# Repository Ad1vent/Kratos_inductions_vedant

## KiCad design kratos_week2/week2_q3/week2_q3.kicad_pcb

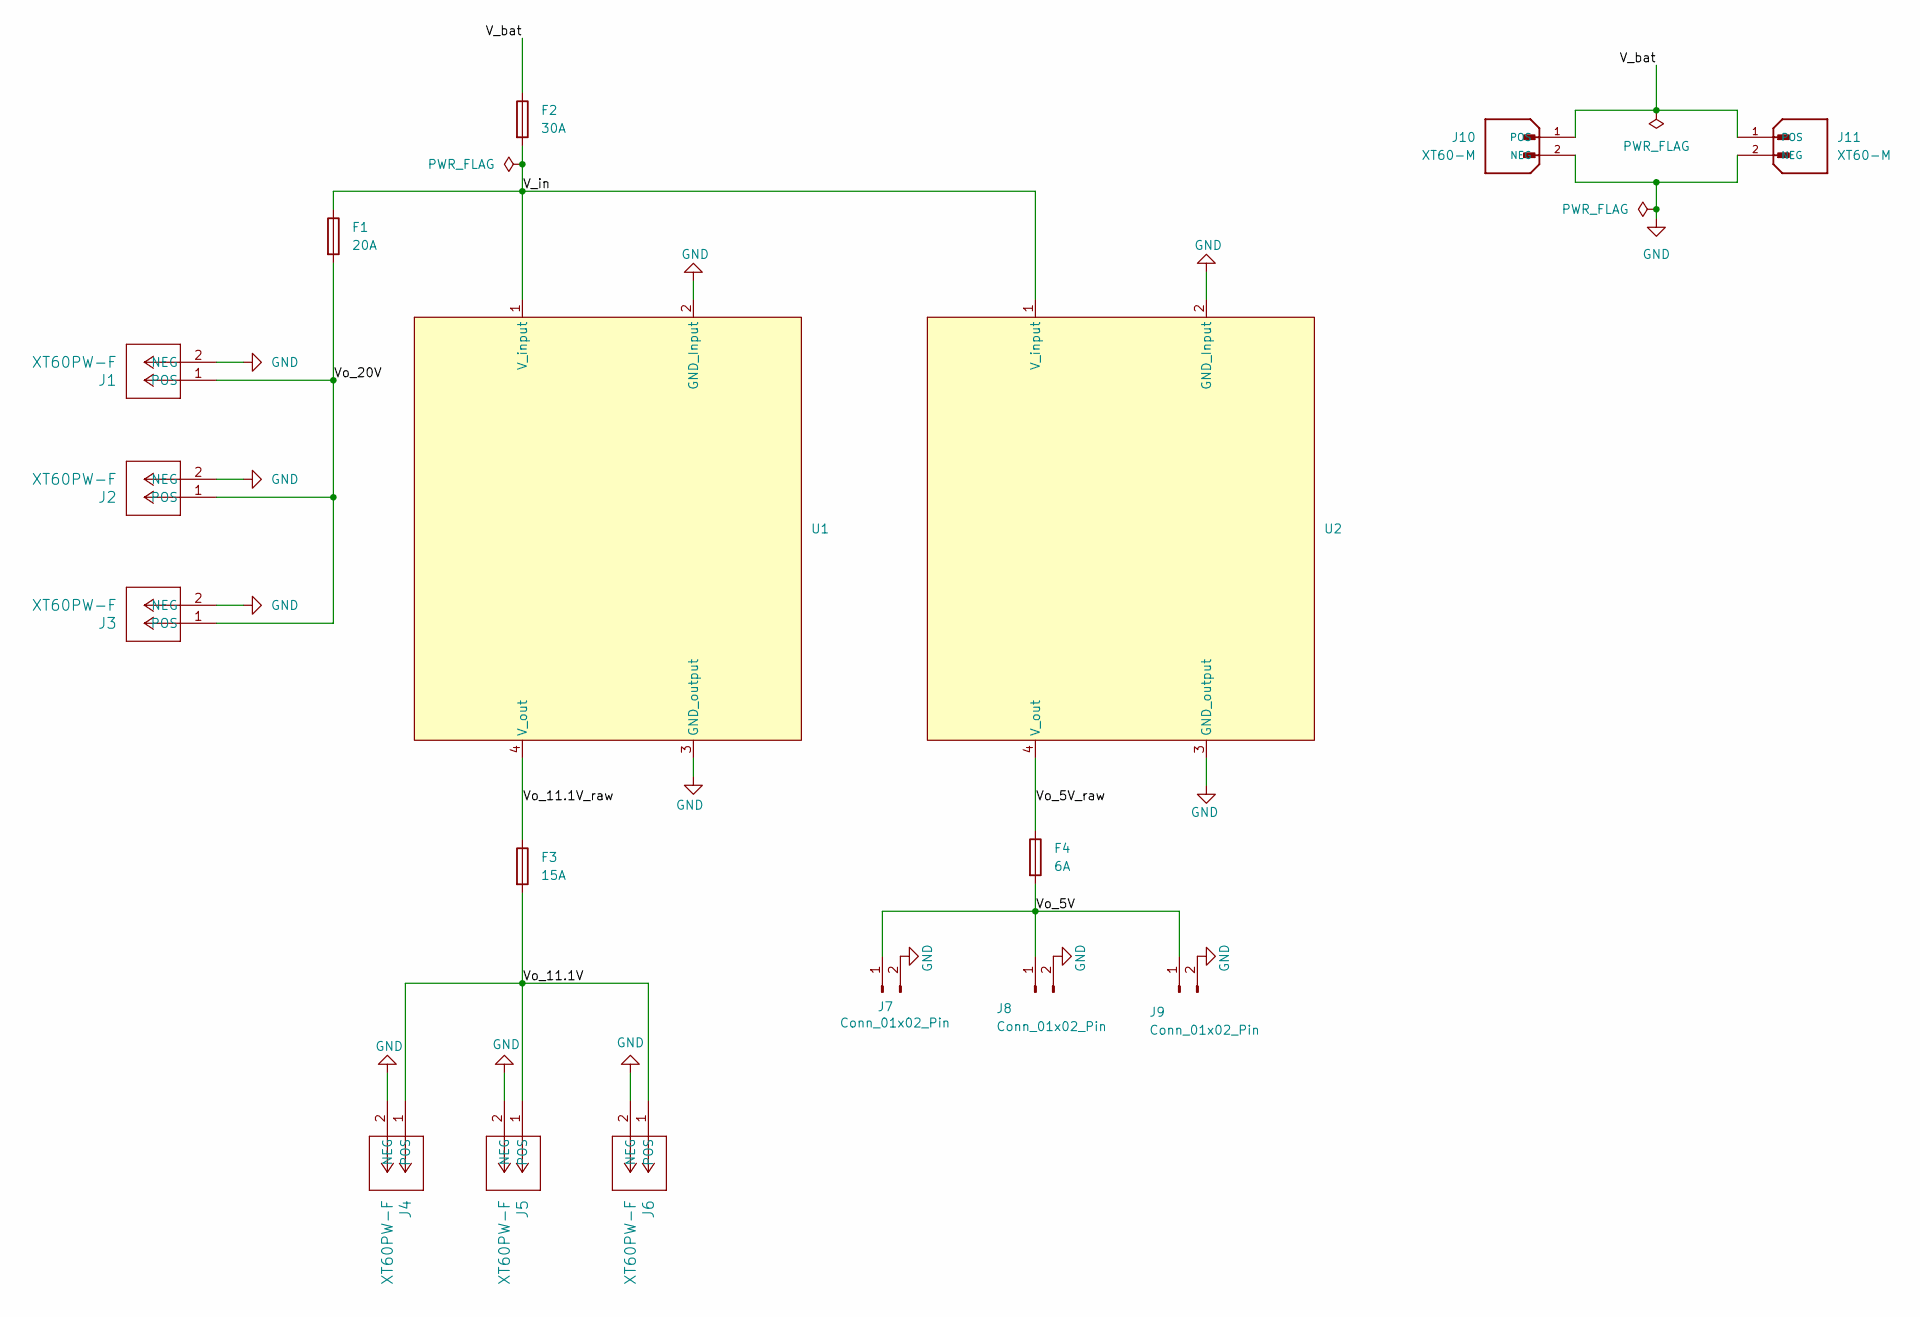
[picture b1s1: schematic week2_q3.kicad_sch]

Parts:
F1: 20A; FuseHolder_Blade_ATO_Littelfuse_FLR_178.6165
F2: 30A; FuseHolder_Blade_ATO_Littelfuse_FLR_178.6165
F3: 15A; FuseHolder_Blade_ATO_Littelfuse_FLR_178.6165
F4: 6A; FuseHolder_Blade_ATO_Littelfuse_FLR_178.6165
J1, J2, J3, J4, J5, J6: XT60PW-F; CONN_XT60PW-F_AMA
J7, J8, J9: Conn_01x02_Pin; PinHeader_1x02_P2.54mm_Vertical
J10, J11: XT60-M; AMASS_XT60-M_1x02_P7.20mm_Vertical; PARTREV V1.2
U1, U2: 20A_DC_buck_conv

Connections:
/V_bat: F2.1, J10.1 (POS), J11.1 (POS)
/V_in: F1.1, F2.2, U1.1 (V_input), U2.1 (V_input)
/Vo_5V: F4.2, J7.1, J8.1, J9.1
/Vo_5V_raw: F4.1, U2.4 (V_out)
/Vo_11.1V: F3.2, J4.1 (POS), J5.1 (POS), J6.1 (POS)
/Vo_11.1V_raw: F3.1, U1.4 (V_out)
/Vo_20V: F1.2, J1.1 (POS), J2.1 (POS), J3.1 (POS)
GND: J1.2 (NEG), J2.2 (NEG), J3.2 (NEG), J4.2 (NEG), J5.2 (NEG), J6.2 (NEG), J7.2, J8.2, J9.2, J10.2 (NEG), J11.2 (NEG), U1.2 (GND_Input), U1.3 (GND_output), U2.2 (GND_Input), U2.3 (GND_output)

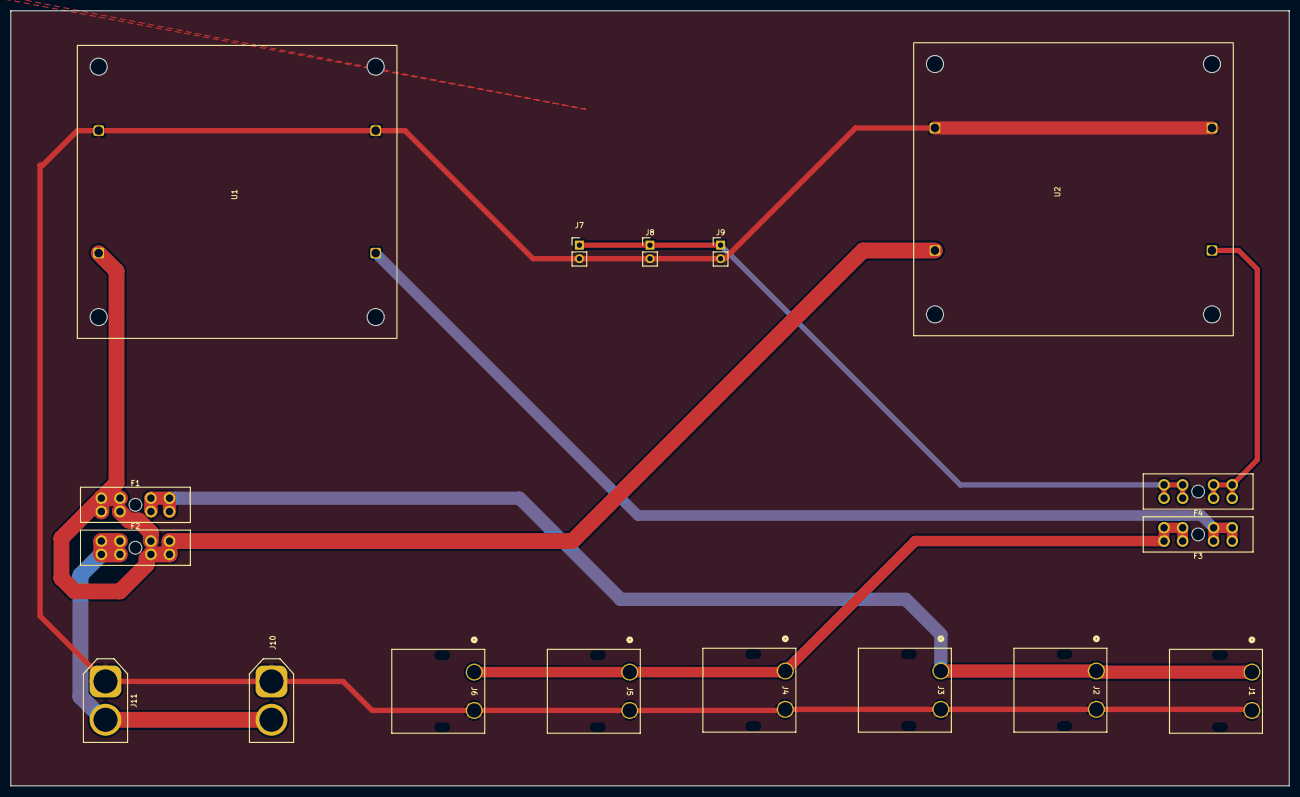
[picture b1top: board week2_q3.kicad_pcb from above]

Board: 2 copper layers, 240.0 x 145.5 mm, 17 parts (0 on the bottom side), 8 nets.

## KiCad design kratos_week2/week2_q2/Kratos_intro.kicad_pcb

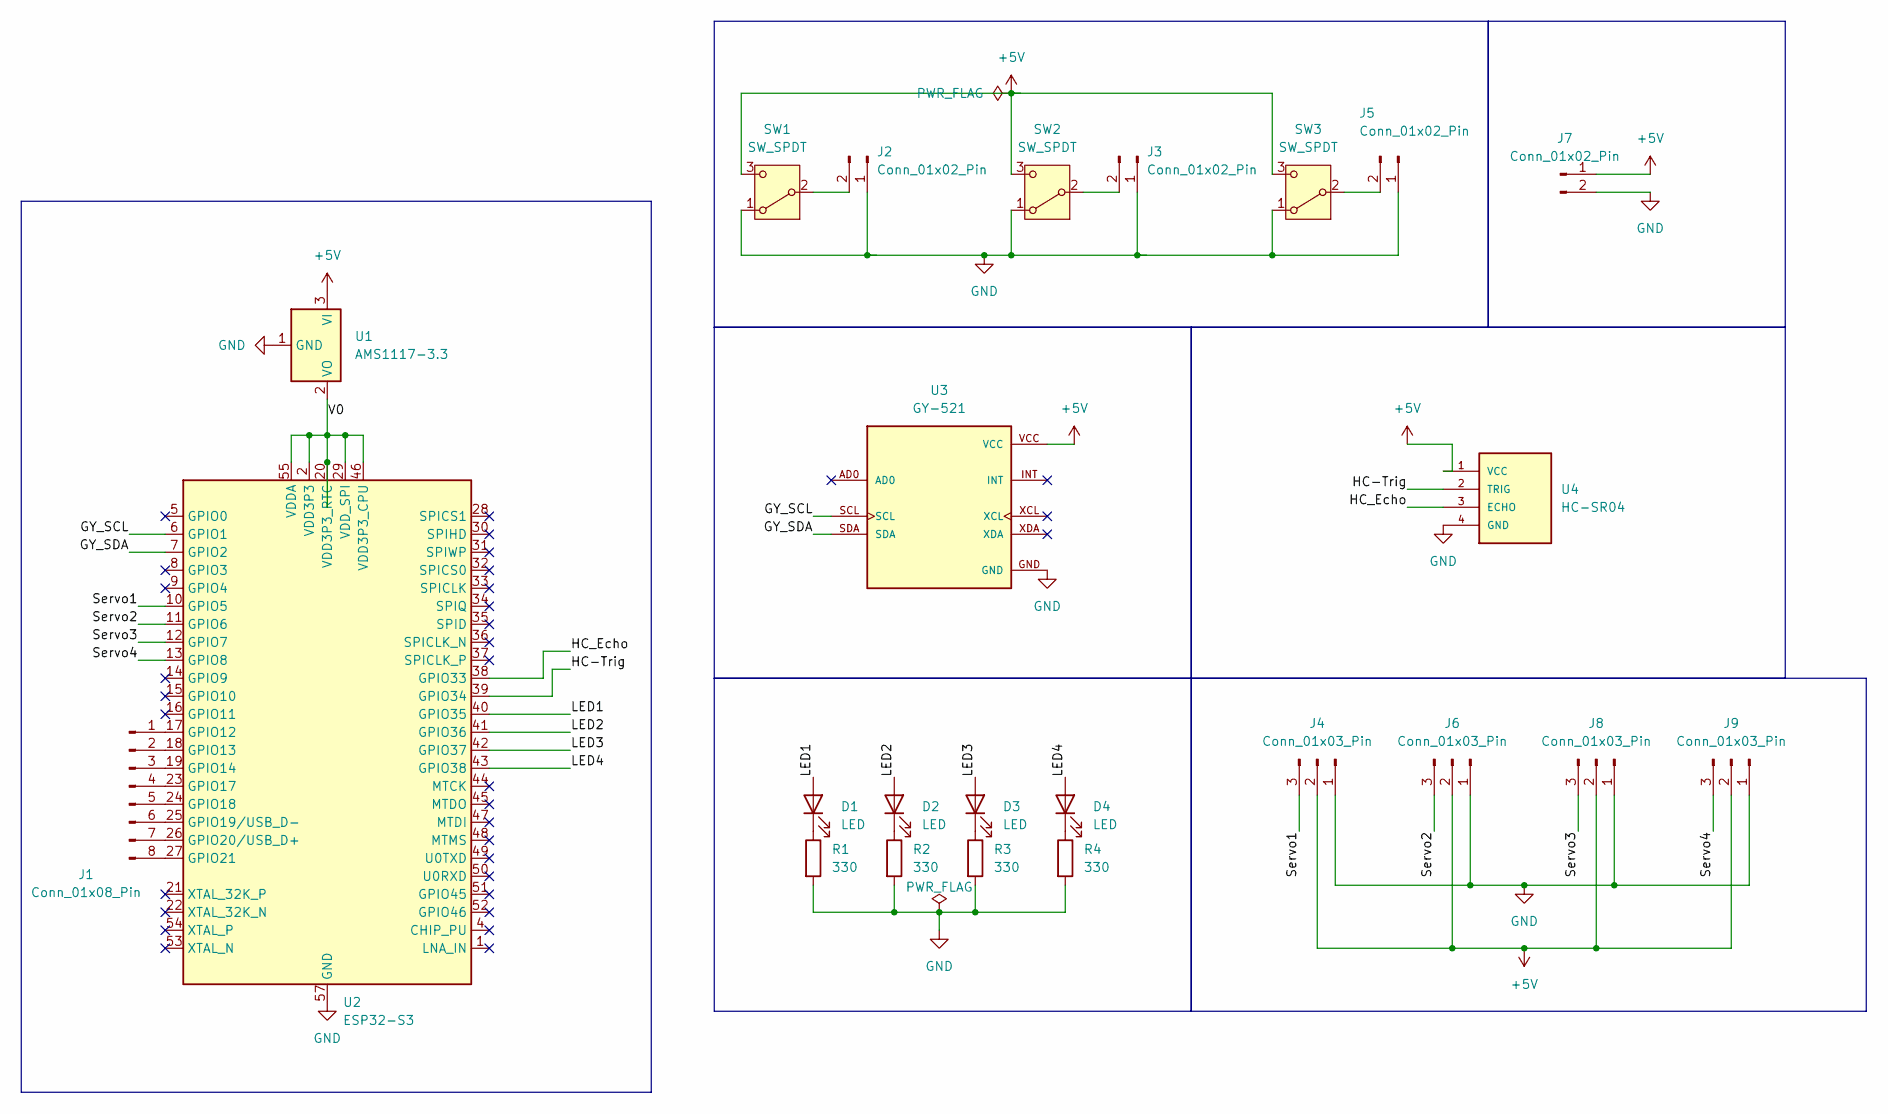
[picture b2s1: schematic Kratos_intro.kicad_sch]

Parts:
D1, D2, D3, D4: LED; LED_D1.8mm_W1.8mm_H2.4mm_Horizontal_O3.81mm_Z4.9mm
J1: Conn_01x08_Pin; Samtec_HPM-08-05-x-S_Straight_1x08_Pitch5.08mm
J2, J3, J5, J7: Conn_01x02_Pin; Samtec_HPM-02-05-x-S_Straight_1x02_Pitch5.08mm
J4, J6, J8, J9: Conn_01x03_Pin; Samtec_HPM-03-05-x-S_Straight_1x03_Pitch5.08mm
R1, R2, R3, R4: 330; R_Axial_DIN0204_L3.6mm_D1.6mm_P2.54mm_Vertical
SW1, SW2, SW3: SW_SPDT; SW_Slide_SPDT_Straight_CK_OS102011MS2Q
U1: AMS1117-3.3; SOT-223-3_TabPin2
U2: ESP32-S3; QFN-56-1EP_7x7mm_P0.4mm_EP4x4mm
U3: GY-521; MODULE_GY-521; PARTREV NA
U4: HC-SR04; XCVR_HC-SR04

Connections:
+5V: J4.2, J6.2, J7.1, J8.2, J9.2, SW1.3 (C), SW2.3 (C), SW3.3 (C), U1.3 (VI), U3.VCC, U4.1 (VCC)
/GY_SCL: U2.6 (GPIO1), U3.SCL
/GY_SDA: U2.7 (GPIO2), U3.SDA
/HC-Trig: U2.39 (GPIO34), U4.2 (TRIG)
/HC_Echo: U2.38 (GPIO33), U4.3 (ECHO)
/LED1: D1.2 (A), U2.40 (GPIO35)
/LED2: D2.2 (A), U2.41 (GPIO36)
/LED3: D3.2 (A), U2.42 (GPIO37)
/LED4: D4.2 (A), U2.43 (GPIO38)
/Servo1: J4.3, U2.10 (GPIO5)
/Servo2: J6.3, U2.11 (GPIO6)
/Servo3: J8.3, U2.12 (GPIO7)
/Servo4: J9.3, U2.13 (GPIO8)
GND: J2.1, J3.1, J4.1, J5.1, J6.1, J7.2, J8.1, J9.1, R1.2, R2.2, R3.2, R4.2, SW1.1 (A), SW2.1 (A), SW3.1 (A), U1.1 (GND), U2.57 (GND), U3.GND, U4.4 (GND)
unnamed: D1.1 (K), R1.1
unnamed: D2.1 (K), R2.1
unnamed: D3.1 (K), R3.1
unnamed: D4.1 (K), R4.1
unnamed: J1.1, U2.17 (GPIO12)
unnamed: J1.2, U2.18 (GPIO13)
unnamed: J1.3, U2.19 (GPIO14)
unnamed: J1.4, U2.23 (GPIO17)
unnamed: J1.5, U2.24 (GPIO18)
unnamed: J1.6, U2.25 (GPIO19/USB_D-)
unnamed: J1.7, U2.26 (GPIO20/USB_D+)
unnamed: J1.8, U2.27 (GPIO21)
unnamed: J2.2, SW1.2 (B)
unnamed: J3.2, SW2.2 (B)
unnamed: J5.2, SW3.2 (B)
unnamed: U1.2 (VO), U2.2 (VDD3P3), U2.3 (VDD3P3), U2.20 (VDD3P3_RTC), U2.29 (VDD_SPI), U2.46 (VDD3P3_CPU), U2.55 (VDDA), U2.56 (VDDA)

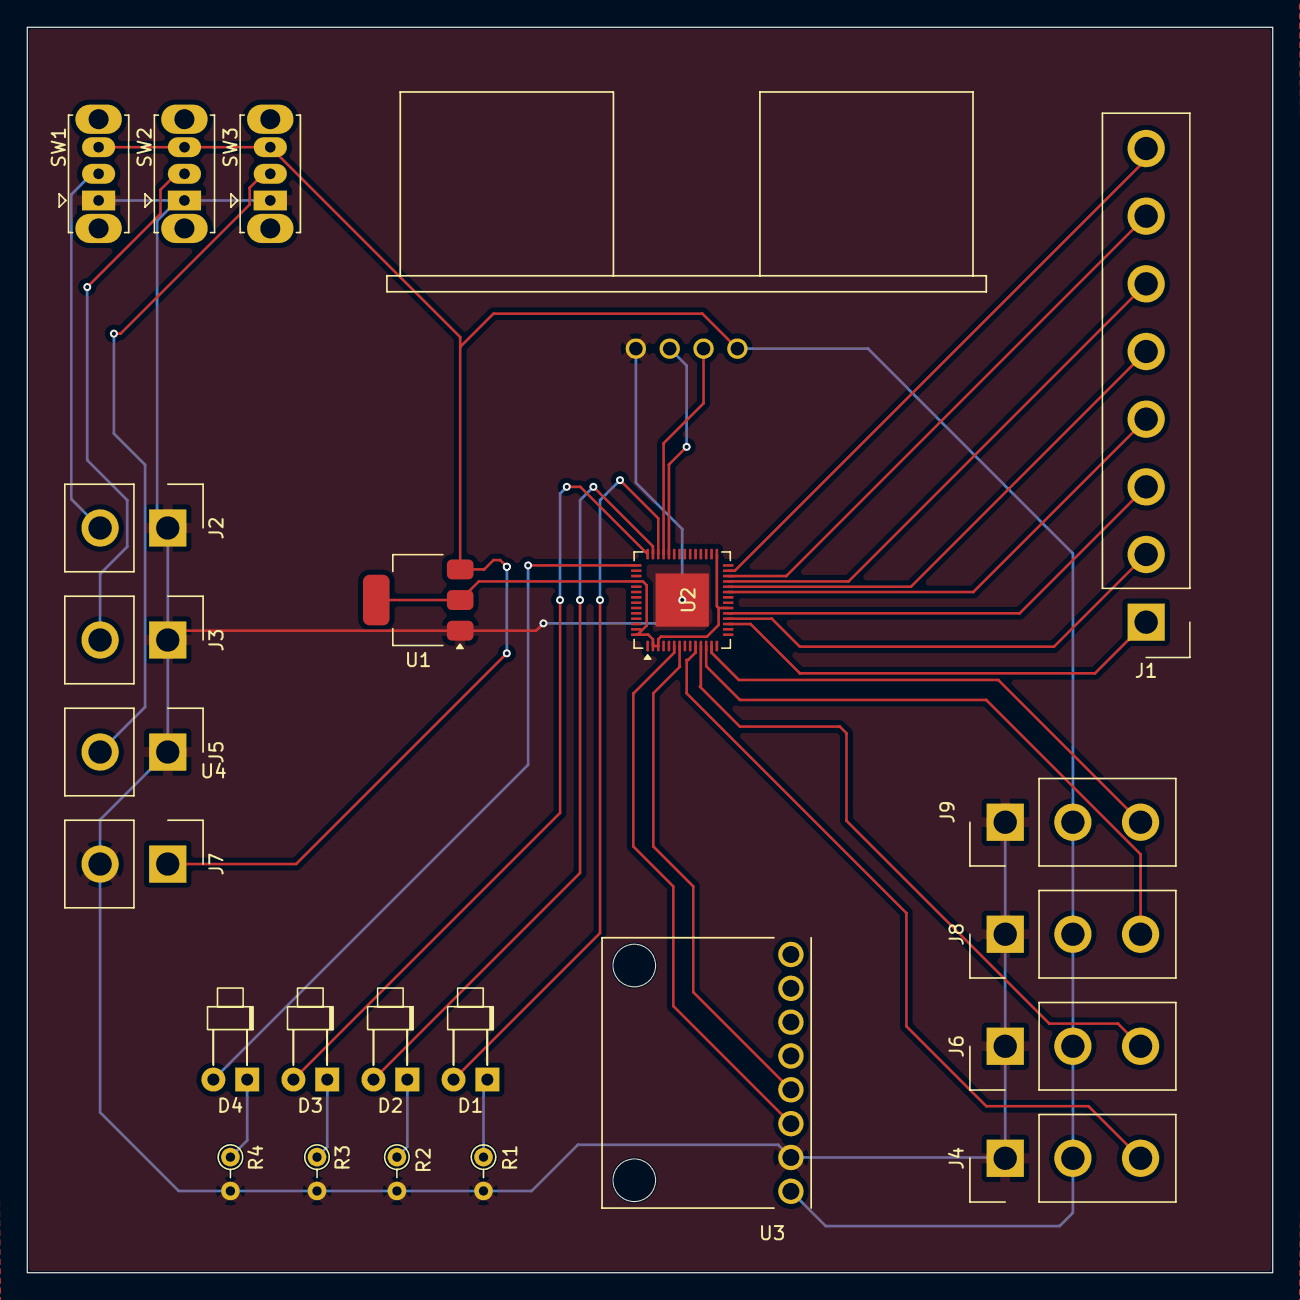
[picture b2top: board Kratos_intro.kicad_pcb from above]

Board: 2 copper layers, 93.5 x 93.5 mm, 24 parts (0 on the bottom side), 30 nets.
